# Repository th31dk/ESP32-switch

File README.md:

# ESP32 Light Switch
Everyday, I'm late to school because I end up falling back asleep. I find it harder to fall back asleep with the lights on, so I designed a automatic light switch with a servo and ESP32

## Bill of Materials
1 0.96" 128x64 OLED Display  
1 GY-302  
1 MAX9814  
1 ESP32 C3 SUPER MINI PLUS  
1 SG90 Servo  
2 M3*12mm SCHS

## PCB
|Schematic|PCB|
|---|---|
|||

## CAD
|Bottom|Top|
|---|---|
|||
Assembly  

## Final Thoughts
I loved designing this since it was something that would make a impact on my life and solve a problem.

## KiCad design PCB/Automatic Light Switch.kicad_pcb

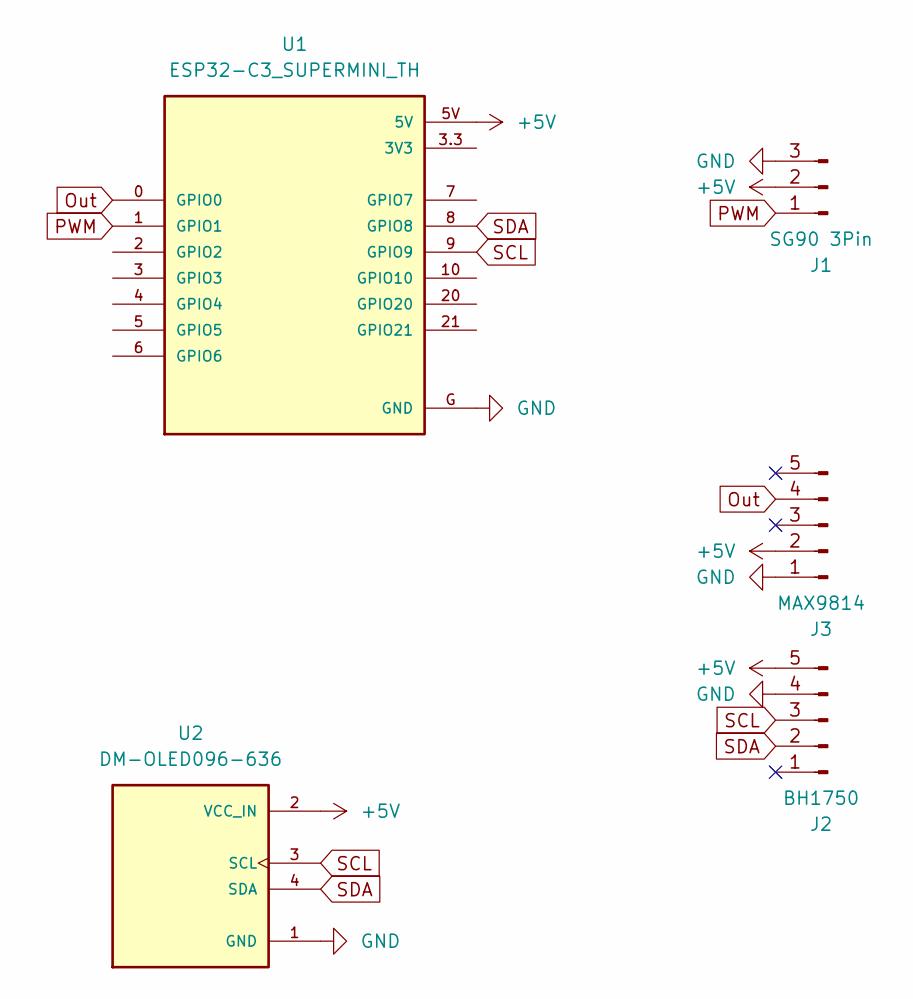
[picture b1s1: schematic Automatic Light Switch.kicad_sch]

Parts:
J1: SG90 3Pin; PinHeader_1x03_P2.54mm_Vertical
J2: BH1750; PinHeader_1x05_P2.54mm_Vertical
J3: MAX9814; PinHeader_1x05_P2.54mm_Vertical
U1: ESP32-C3_SUPERMINI_TH; MODULE_ESP32-C3_SUPERMINI_TH
U2: DM-OLED096-636; MODULE_DM-OLED096-636; PARTREV 2018-09-10

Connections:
+5V: J1.2, J2.5, J3.2, U1.5V, U2.2 (VCC_IN)
GND: J1.3, J2.4, J3.1, U1.G (GND), U2.1 (GND)
Out: J3.4, U1.0 (GPIO0)
PWM: J1.1, U1.1 (GPIO1)
SCL: J2.3, U1.9 (GPIO9), U2.3 (SCL)
SDA: J2.2, U1.8 (GPIO8), U2.4 (SDA)

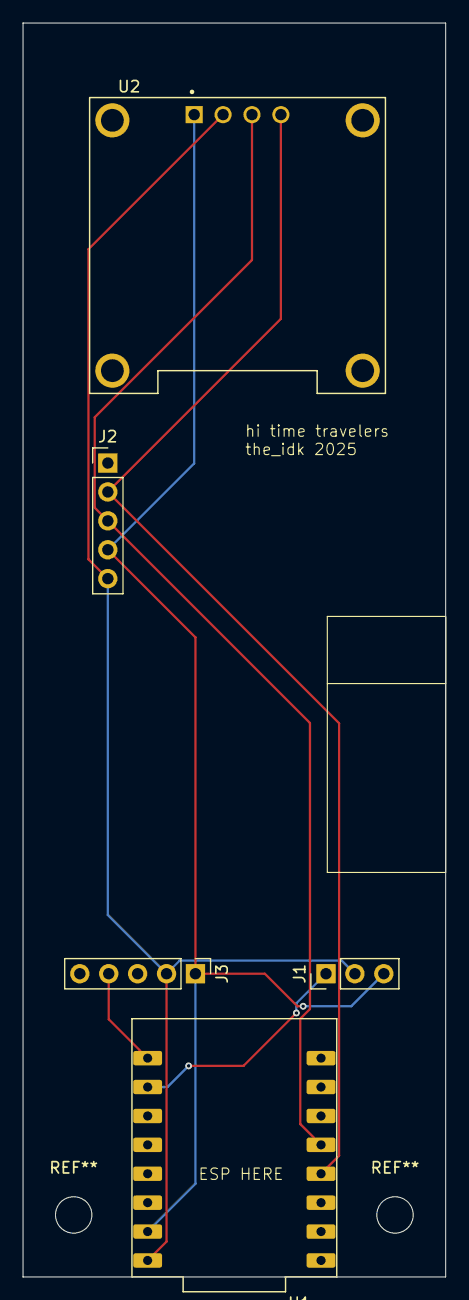
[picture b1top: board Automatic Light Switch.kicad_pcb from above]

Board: 2 copper layers, 37.1 x 110.2 mm, 5 parts (0 on the bottom side), 6 nets.

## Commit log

2025-12-12 Rename project to 'ESP32 Light Switch'
    Updated project title for clarity and focus.
